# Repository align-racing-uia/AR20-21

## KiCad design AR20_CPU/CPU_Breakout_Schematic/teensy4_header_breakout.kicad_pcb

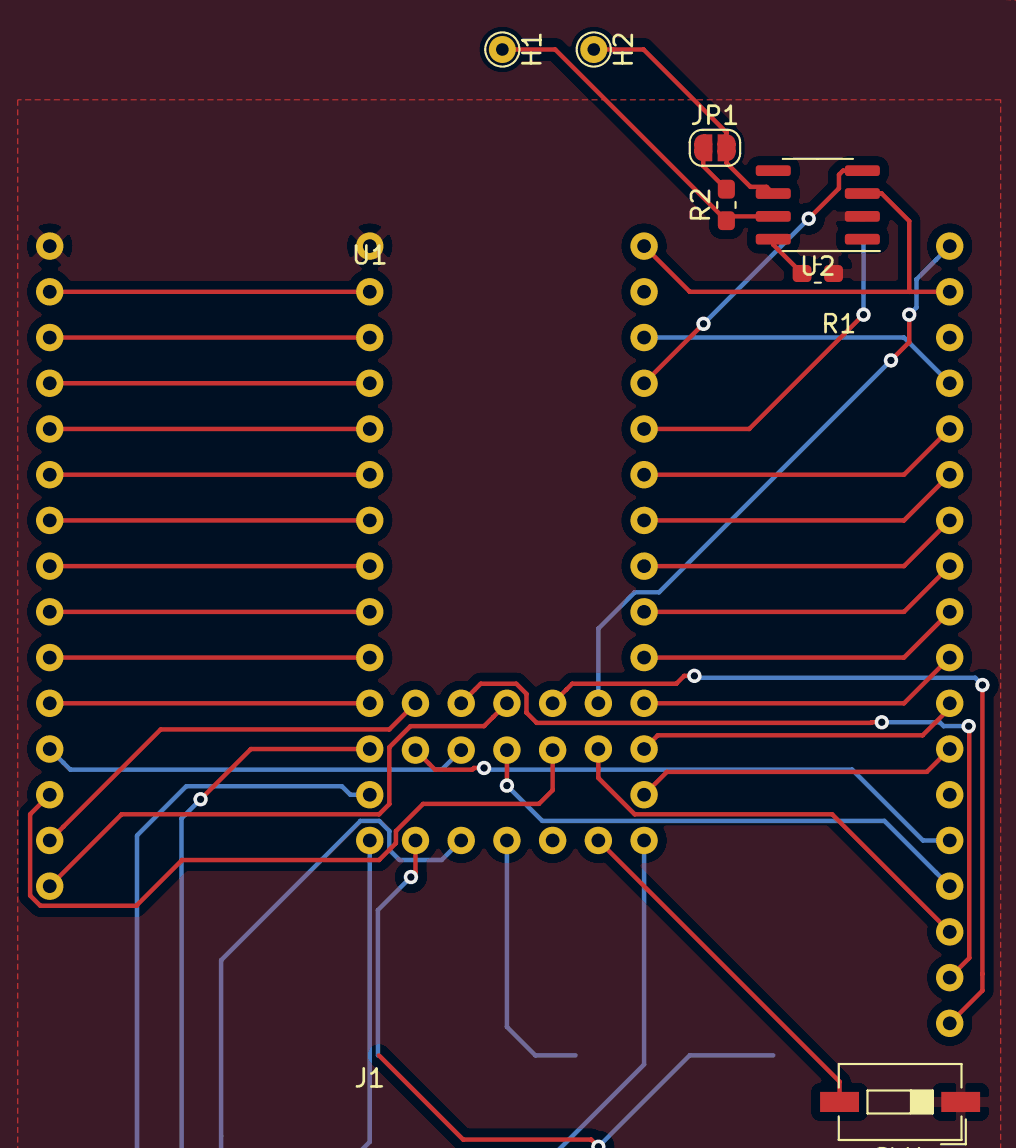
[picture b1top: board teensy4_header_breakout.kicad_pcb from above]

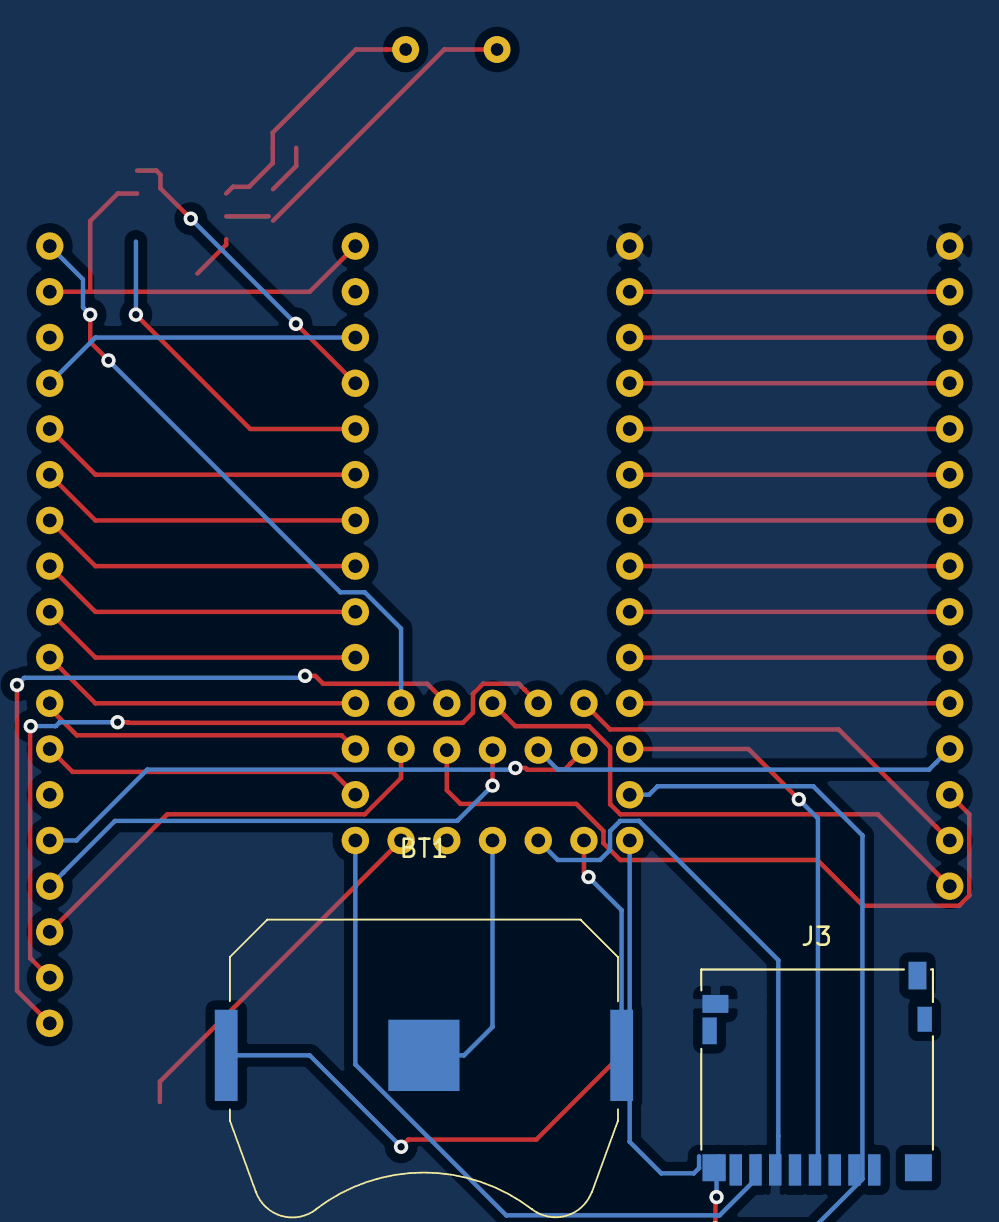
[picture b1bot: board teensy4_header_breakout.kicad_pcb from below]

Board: 4 copper layers, 11 parts (2 on the bottom side), 47 nets.

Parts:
BT1: 2.7V; BatteryHolder_Keystone_3034_1x20mm
H1: CANH_out; TestPoint_THTPad_D1.5mm_Drill0.7mm
H2: CANL_out; TestPoint_THTPad_D1.5mm_Drill0.7mm
J1: Conn_2Rows-34Pins; PINS_IO_TEENSY
J3: Micro_SD_Card; microSD_HC_Hirose_DM3D-SF
JP1: SolderJumper_2_Open; SolderJumper-2_P1.3mm_Open_RoundedPad1.0x1.5mm
R1: 60; R_0603_1608Metric_Pad1.05x0.95mm_HandSolder
R2: 120; R_0603_1608Metric_Pad1.05x0.95mm_HandSolder
SW1: SW_SPST; SW_DIP_SPSTx01_Slide_6.7x4.1mm_W6.73mm_P2.54mm_LowProfile_J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
U1: Teensy_pins; Teensy_40_footprint
U2: MCP2551-I-SN; SOIC-8_3.9x4.9mm_P1.27mm

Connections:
0_RX1: J1.3, U1.3
1_TX1: J1.5, U1.5
2_OUT2: J1.7, U1.7
3.3V: J1.12, U1.6
3V3: J3.4, U1.30
3_LRCLK2: J1.9, U1.9
4_BCLK2: J1.11, U1.11
5_IN2: J1.13, U1.13
6_OUT1D: J1.15, U1.15
7_RX2_OUT1A: J1.17, U1.17
8_IN1: J1.19, U1.19
9_OUT1C: J1.21, U1.21
10_CS: J3.2, U1.23
11_MOSI: J3.7, U1.25
12_MISO: J3.8, U1.27
13(LED): J3.5, U1.28
14_A0: J1.28, U1.26
15_A1: J1.26, U1.24
16_A2: J1.24, U1.22
17_A3: J1.22, U1.20
18_A4: J1.20, U1.18
19_A5: J1.18, U1.16
20_A6: J1.16, U1.14
21_A7: J1.14, U1.12
22_CTX1: U1.10, U2.1
23_CRX1: U1.8, U2.4
24_A10: J1.34, U1.34
25_A11: J1.35, U1.35
26_A12: J1.36, U1.36
27_A13: J1.37, U1.37
28_RX7: J1.38, U1.38
29_TX7: J1.39, U1.39
30_CRX3: J1.40, U1.40
31_CTX3: J1.41, U1.41
32_OUT1B: J1.42, U1.42
33_MCLK2: J1.2, U1.43
GND_1: J1.6, U1.4
GND_BATT: BT1.2, U1.31
Ground: J1.1, J3.6, J3.9, R1.1, SW1.1, U1.1, U2.2
unnamed: H1.1, R2.1, U2.7
unnamed: H2.1, JP1.2, U2.6
unnamed: JP1.1, R2.2
unnamed: R1.2, U2.8
ON_OFF: SW1.2, U1.33
PROGRAMM: J1.32, U1.32
VBAT: BT1.1, U1.29
Vinn_5V: J1.4, U1.2, U2.3

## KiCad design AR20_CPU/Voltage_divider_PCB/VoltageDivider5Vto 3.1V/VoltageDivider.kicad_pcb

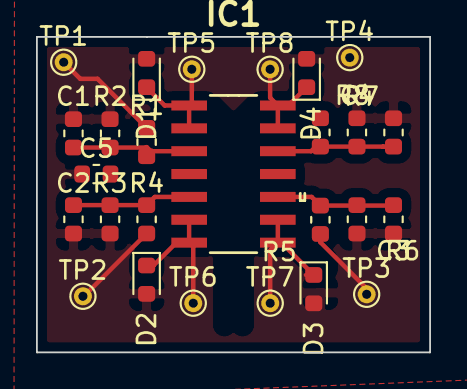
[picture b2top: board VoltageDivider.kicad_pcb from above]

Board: 2 copper layers, 21.8 x 17.5 mm, 26 parts (0 on the bottom side), 13 nets.

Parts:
C1, C2, C3, C4: 1.5n; C_0603_1608Metric
C5: C; C_0603_1608Metric
D1, D2, D3, D4: 3V; D_0603_1608Metric
IC1: LM324DRG3; SOIC127P600X175-14N
R1, R3, R5, R7: 10k; R_0603_1608Metric
R2, R4, R6, R8: 20k; R_0603_1608Metric
TP1, TP2, TP3, TP4, TP5, TP6, TP7, TP8: TestPoint; TestPoint_THTPad_D1.0mm_Drill0.5mm

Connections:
GND: C1.2, C2.2, C3.2, C4.2, C5.1, D1.2, D2.2, D3.2, D4.2, R2.2, R4.2, R6.2, R8.2
IN1+: C1.1, IC1.3, R1.2, R2.1
IN2+: C2.1, IC1.5, R3.2, R4.1
IN3+: C3.1, IC1.10, R5.2, R6.1
IN4+: C4.1, IC1.12, R7.2, R8.1
Out1: D1.1, IC1.1, IC1.2, TP5.1
Out2: D2.1, IC1.6, IC1.7, TP6.1
Out3: D3.1, IC1.8, IC1.9, TP7.1
Out4: D4.1, IC1.13, IC1.14, TP8.1
Sensor_Input_1: R1.1, TP1.1
Sensor_Input_2: R3.1, TP2.1
Sensor_Input_3: R5.1, TP3.1
Sensor_Input_4: R7.1, TP4.1

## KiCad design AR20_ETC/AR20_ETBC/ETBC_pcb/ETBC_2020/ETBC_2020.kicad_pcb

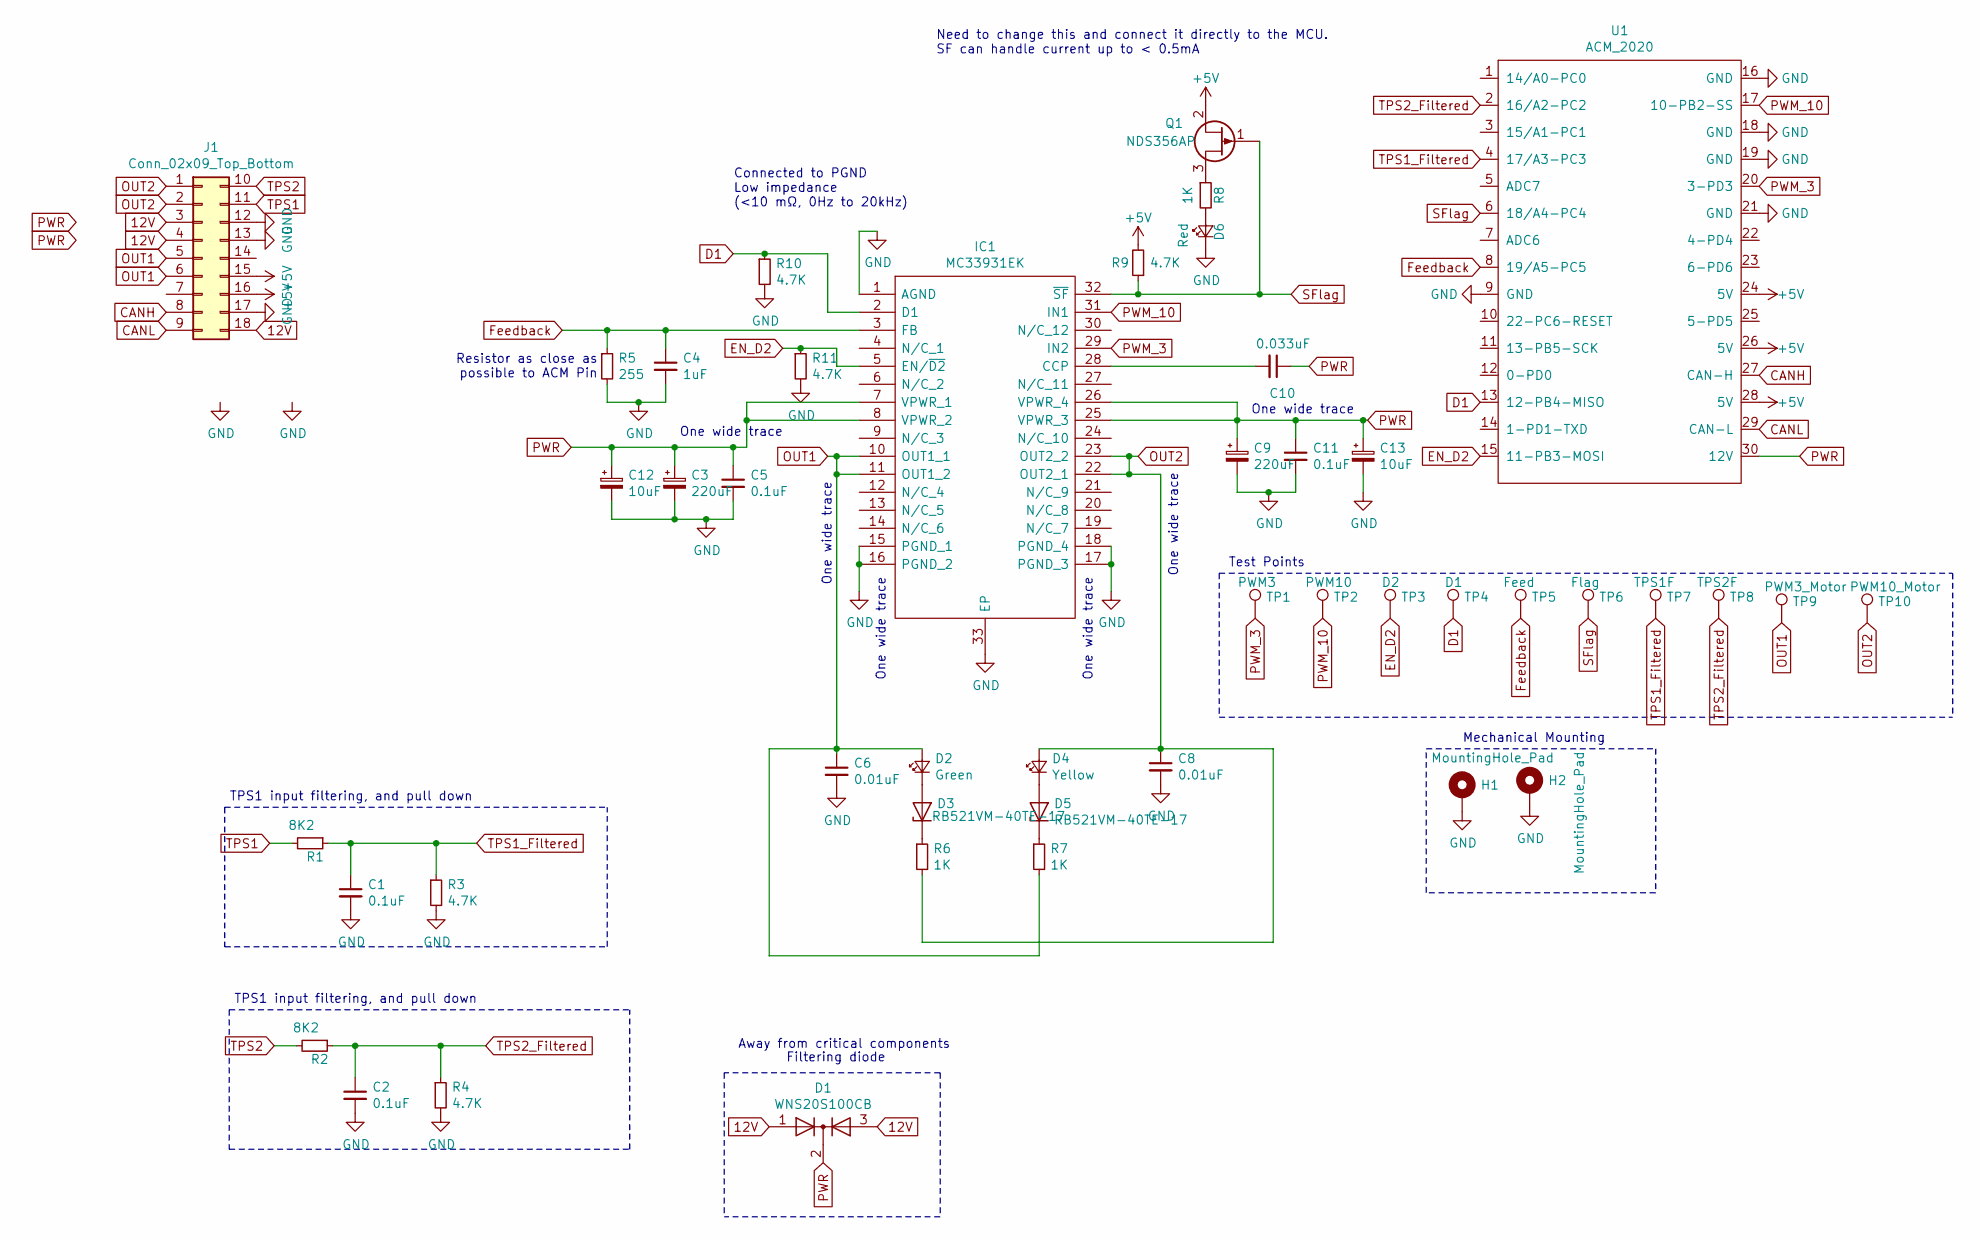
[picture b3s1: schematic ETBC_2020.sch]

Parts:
C1, C2, C5, C11: 0.1uF; C_0603_1608Metric_Pad1.05x0.95mm_HandSolder
C3, C9: 220uF; CP_Elec_6.3x7.7
C4: 1uF; C_0603_1608Metric_Pad1.05x0.95mm_HandSolder
C6, C8: 0.01uF; C_0603_1608Metric_Pad1.05x0.95mm_HandSolder
C10: 0.033uF; C_0603_1608Metric_Pad1.05x0.95mm_HandSolder
C12, C13: 10uF; CP_EIA-3216-10_Kemet-I_Pad1.58x1.35mm_HandSolder
D1: WNS20S100CB; TO-263-3_TabPin2
D2: Green; D_1206_3216Metric_Pad1.42x1.75mm_HandSolder
D3, D5: RB521VM-40TE-17; D_SOD-323F
D4: Yellow; D_1206_3216Metric_Pad1.42x1.75mm_HandSolder
D6: Red; D_1206_3216Metric_Pad1.42x1.75mm_HandSolder
H1, H2: MountingHole_Pad; MountingHole_3.2mm_M3_Pad_Via
IC1: MC33931EK; SOP65P1030X245-33N; Manufacturer_Part_Number MC33931EK; Mouser Part Number 841-MC33931EK
J1: Conn_02x09_Top_Bottom; JAE_MX23A18NF1
Q1: NDS356AP; SOT-23
R1, R2: 8K2; R_0603_1608Metric_Pad1.05x0.95mm_HandSolder
R3, R4, R9, R10, R11: 4.7K; R_0603_1608Metric_Pad1.05x0.95mm_HandSolder
R5: 255; R_0603_1608Metric_Pad1.05x0.95mm_HandSolder
R6, R7, R8: 1K; R_0603_1608Metric_Pad1.05x0.95mm_HandSolder
TP1: PWM3; TestPoint_Keystone_5000-5004_Miniature
TP2: PWM10; TestPoint_Keystone_5000-5004_Miniature
TP3: D2; TestPoint_Keystone_5000-5004_Miniature
TP4: D1; TestPoint_Keystone_5000-5004_Miniature
TP5: Feed; TestPoint_Keystone_5000-5004_Miniature
TP6: Flag; TestPoint_Keystone_5000-5004_Miniature
TP7: TPS1F; TestPoint_Keystone_5000-5004_Miniature
TP8: TPS2F; TestPoint_Keystone_5000-5004_Miniature
TP9: PWM3_Motor; TestPoint_Keystone_5000-5004_Miniature
TP10: PWM10_Motor; TestPoint_Keystone_5000-5004_Miniature
U1: ACM_2020; ACM_2020_Footprint_wo_silk

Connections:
12V: D1.1 (A), D1.3 (A), J1.3, J1.4, J1.18
+5V: J1.15, J1.16, Q1.2 (S), R9.2, U1.24 (5V), U1.26 (5V), U1.28 (5V)
CANH: J1.8, U1.27 (CAN-H)
CANL: J1.9, U1.29 (CAN-L)
D1: IC1.2 (D1), R10.1, TP4.1, U1.13 (12-PB4-MISO)
EN_D2: IC1.5 (EN/~D2), R11.1, TP3.1, U1.15 (11-PB3-MOSI)
Feedback: C4.1, IC1.3 (FB), R5.1, TP5.1, U1.8 (19/A5-PC5)
GND: C1.2, C2.2, C3.2, C4.2, C5.2, C6.2, C8.2, C9.2, C11.2, C12.2, C13.2, D6.1 (K), H1.1, H2.1, IC1.1 (AGND), IC1.15 (PGND_1), IC1.16 (PGND_2), IC1.17 (PGND_3), IC1.18 (PGND_4), IC1.33 (EP), J1.12, J1.13, J1.17, R3.2, R4.2, R5.2, R10.2, R11.2, U1.9 (GND), U1.16 (GND), U1.18 (GND), U1.19 (GND), U1.21 (GND)
unnamed: C10.2, IC1.28 (CCP)
unnamed: D2.1 (K), D3.2 (A)
unnamed: D3.1 (K), R6.1
unnamed: D4.1 (K), D5.2 (A)
unnamed: D5.1 (K), R7.1
unnamed: D6.2 (A), R8.2
unnamed: Q1.3 (D), R8.1
OUT1: C6.1, D2.2 (A), IC1.10 (OUT1_1), IC1.11 (OUT1_2), J1.5, J1.6, R7.2, TP9.1
OUT2: C8.1, D4.2 (A), IC1.22 (OUT2_1), IC1.23 (OUT2_2), J1.1, J1.2, R6.2, TP10.1
PWM_3: IC1.29 (IN2), TP1.1, U1.20 (3-PD3)
PWM_10: IC1.31 (IN1), TP2.1, U1.17 (10-PB2-SS)
PWR: C3.1, C5.1, C9.1, C10.1, C11.1, C12.1, C13.1, D1.2 (K), IC1.7 (VPWR_1), IC1.8 (VPWR_2), IC1.25 (VPWR_3), IC1.26 (VPWR_4), U1.30 (12V)
SFlag: IC1.32 (~SF), Q1.1 (G), R9.1, TP6.1, U1.6 (18/A4-PC4)
TPS1: J1.11, R1.2
TPS1_Filtered: C1.1, R1.1, R3.1, TP7.1, U1.4 (17/A3-PC3)
TPS2: J1.10, R2.2
TPS2_Filtered: C2.1, R2.1, R4.1, TP8.1, U1.2 (16/A2-PC2)

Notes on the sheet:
TPS1 input filtering, and pull down
Resistor as close as possible to ACM Pin
Filtering diode
Connected to PGND Low impedance (<10 mΩ, 0Hz to 20kHz)
One wide trace
Need to change this and connect it directly to the MCU. SF can handle current up to < 0.5mA
Away from critical components
Mechanical Mounting
Test Points

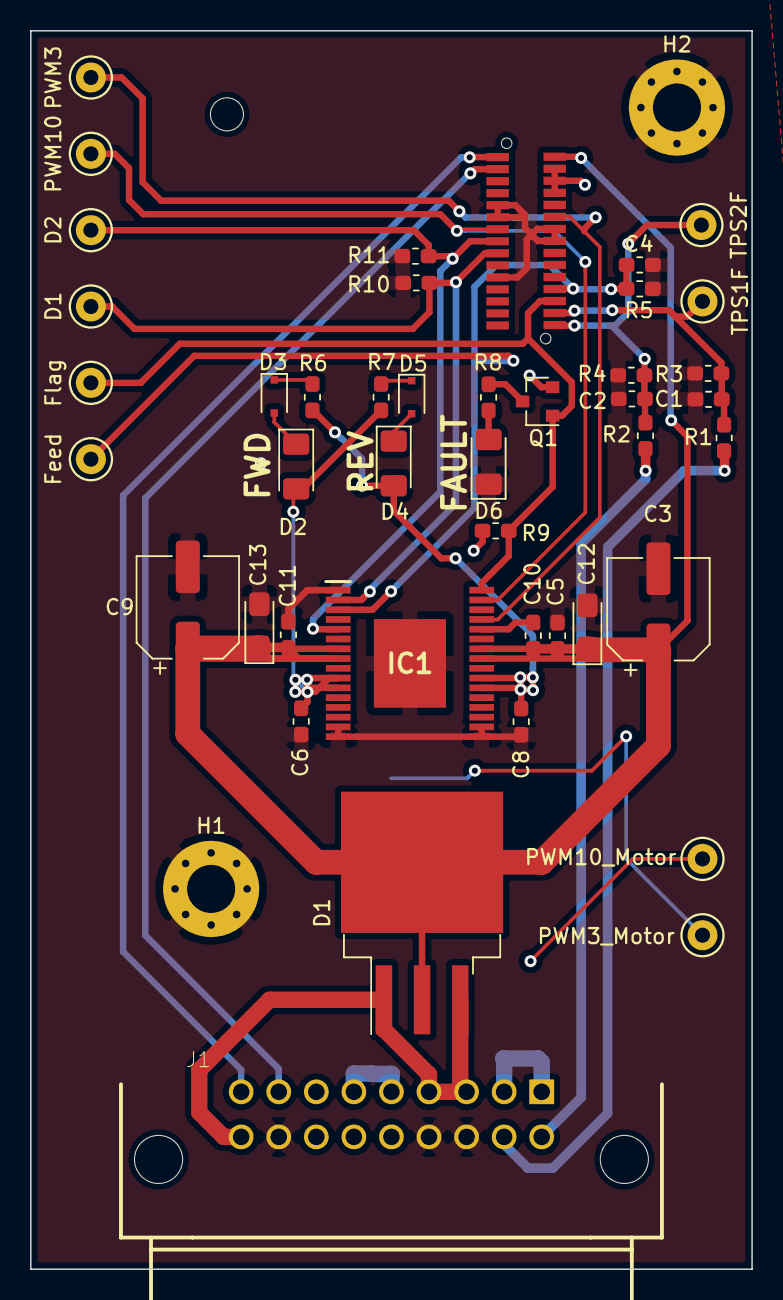
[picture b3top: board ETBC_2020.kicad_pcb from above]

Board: 2 copper layers, 48.0 x 82.4 mm, 45 parts (0 on the bottom side), 25 nets.

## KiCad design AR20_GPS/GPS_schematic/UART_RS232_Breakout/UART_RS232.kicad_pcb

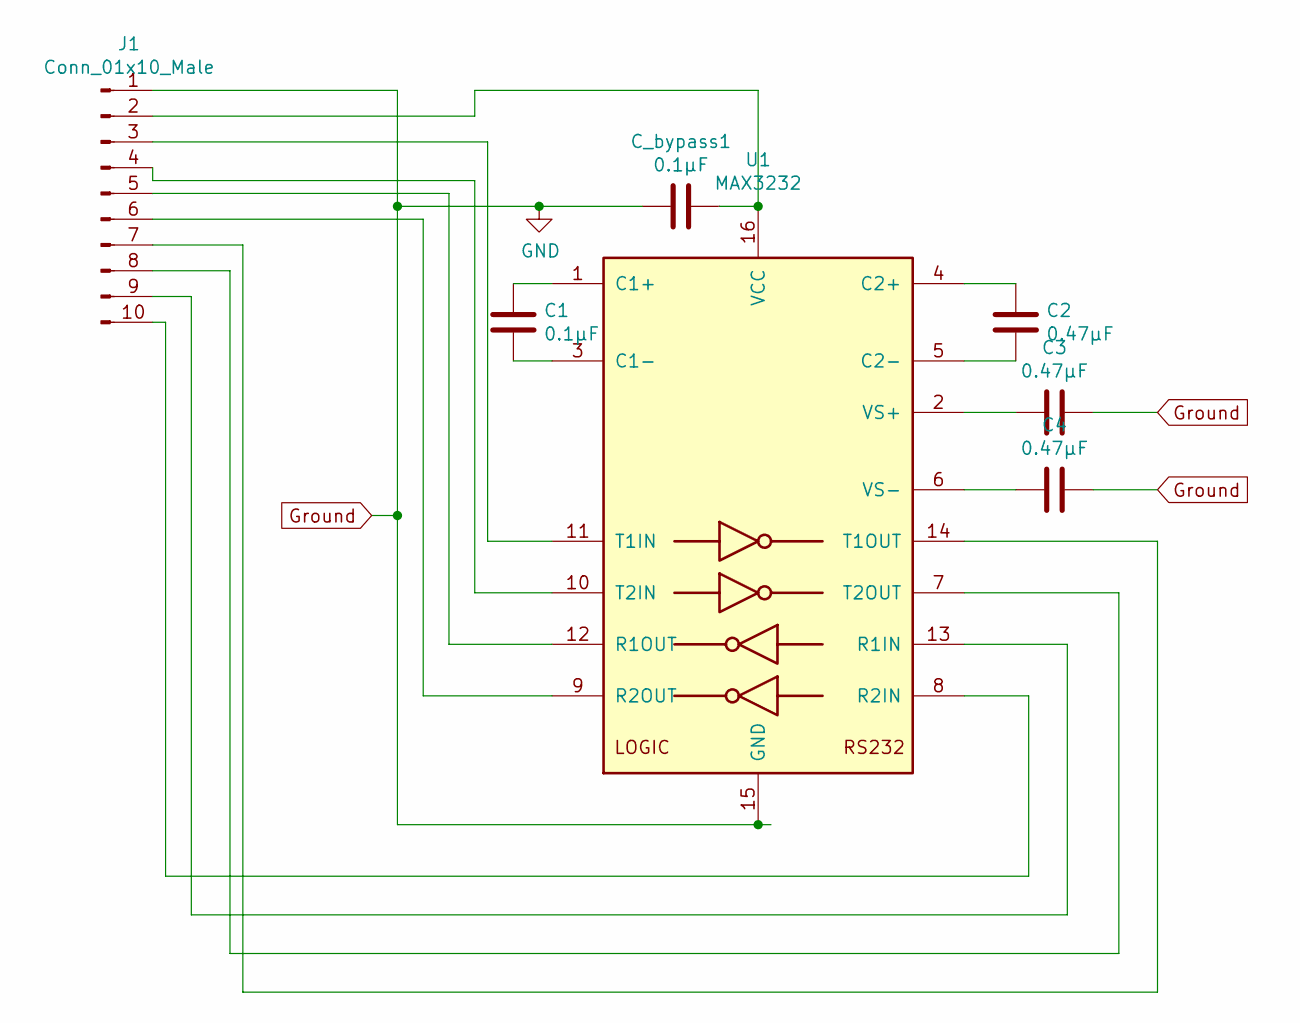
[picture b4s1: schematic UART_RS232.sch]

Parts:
C1: 0.1µF; C_Disc_D8.0mm_W5.0mm_P5.00mm
C2, C3, C4: 0.47µF; C_Disc_D8.0mm_W5.0mm_P5.00mm
C_bypass1: 0.1µF; C_Disc_D8.0mm_W5.0mm_P5.00mm
J1: Conn_01x10_Male; PinHeader_1x10_P2.54mm_Horizontal
U1: MAX3232; DIP-16_W7.62mm

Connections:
Ground: C3.2, C4.2, C_bypass1.1, J1.1, U1.15 (GND)
unnamed: C1.1, U1.1 (C1+)
unnamed: C1.2, U1.3 (C1-)
unnamed: C2.1, U1.4 (C2+)
unnamed: C2.2, U1.5 (C2-)
unnamed: C3.1, U1.2 (VS+)
unnamed: C4.1, U1.6 (VS-)
unnamed: C_bypass1.2, J1.2, U1.16 (VCC)
unnamed: J1.3, U1.11 (T1IN)
unnamed: J1.4, U1.10 (T2IN)
unnamed: J1.5, U1.12 (R1OUT)
unnamed: J1.6, U1.9 (R2OUT)
unnamed: J1.7, U1.14 (T1OUT)
unnamed: J1.8, U1.7 (T2OUT)
unnamed: J1.9, U1.13 (R1IN)
unnamed: J1.10, U1.8 (R2IN)

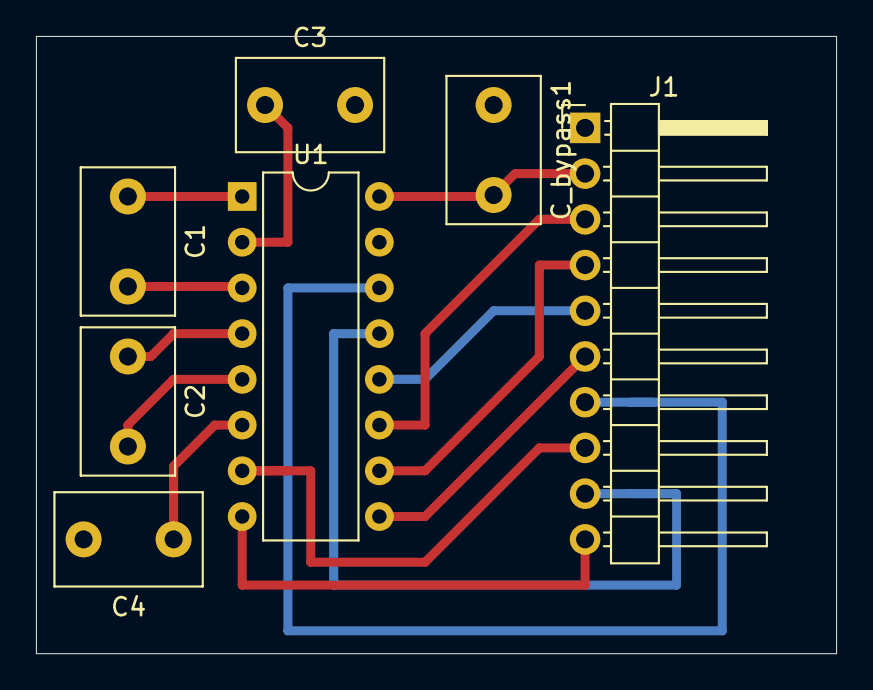
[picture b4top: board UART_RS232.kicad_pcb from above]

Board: 2 copper layers, 44.5 x 34.3 mm, 7 parts (0 on the bottom side), 16 nets.

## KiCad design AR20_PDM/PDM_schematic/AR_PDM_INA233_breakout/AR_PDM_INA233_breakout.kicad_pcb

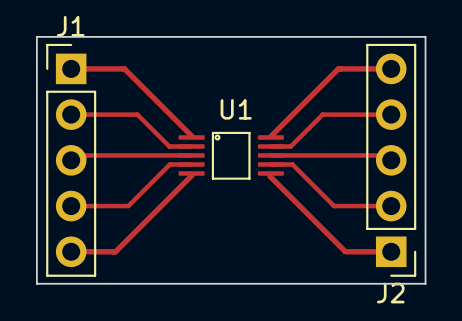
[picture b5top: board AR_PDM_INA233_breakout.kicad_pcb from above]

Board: 2 copper layers, 21.6 x 13.7 mm, 3 parts (0 on the bottom side), 10 nets.

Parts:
J1, J2: Conn_01x05_Male; PinHeader_1x05_P2.54mm_Vertical
U1: INA233

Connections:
GND: J2.2, U1.7
IN+: J2.5, U1.10
IN-: J2.4, U1.9
unnamed: J1.1, U1.1
unnamed: J1.2, U1.2
unnamed: J1.3, U1.3
unnamed: J1.4, U1.4
unnamed: J1.5, U1.5
VBUS: J2.3, U1.8
VS: J2.1, U1.6

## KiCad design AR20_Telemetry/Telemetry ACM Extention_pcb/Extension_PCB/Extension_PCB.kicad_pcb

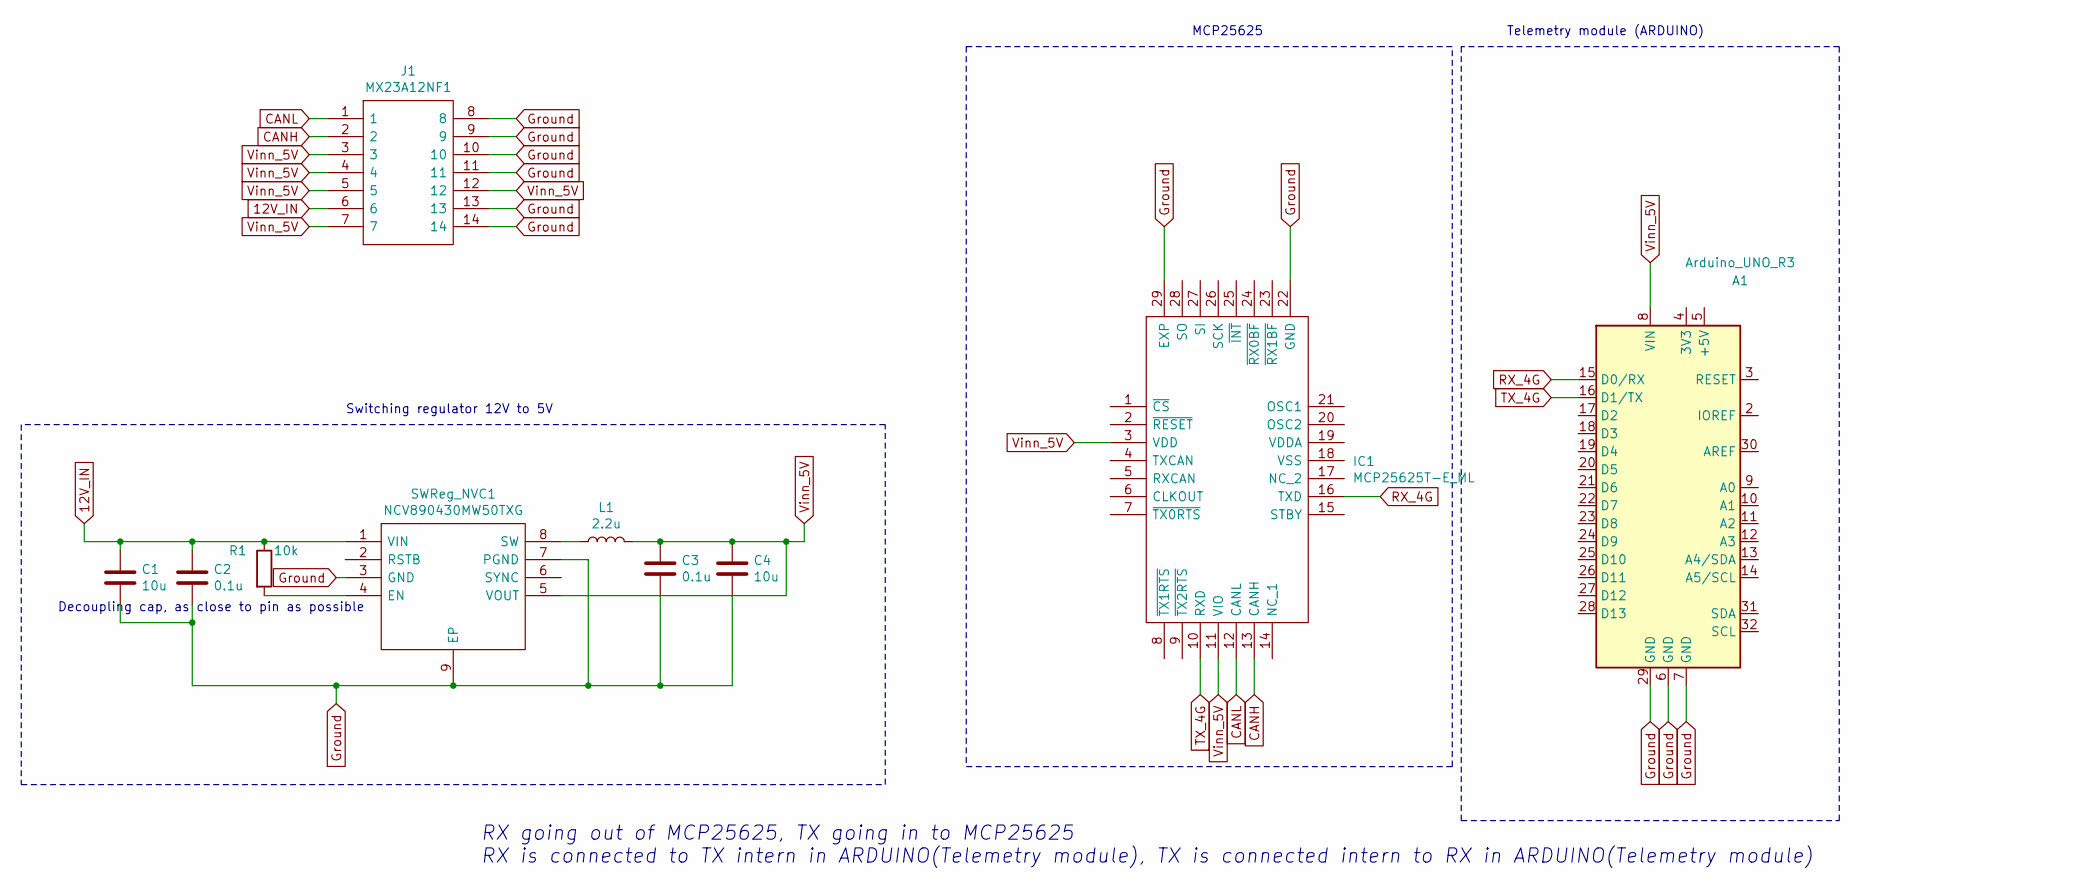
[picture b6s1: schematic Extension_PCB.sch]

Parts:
A1: Arduino_UNO_R3; Arduino_UNO_R3_WithMountingHoles_telemetry
C1, C4: 10u; C_0603_1608Metric
C2, C3: 0.1u; C_0603_1608Metric
IC1: MCP25625T-E_ML; QFN65P600X600X100-29N-D; Manufacturer_Part_Number MCP25625T-E/ML; Mouser Part Number 579-MCP25625T-E/ML
J1: MX23A12NF1; Manufacturer_Part_Number MX23A12NF1; Mouser Part Number 656-MX23A12NF1
L1: 2.2u; L_0603_1608Metric
R1: 10k; R_0603_1608Metric
SWReg_NVC1: NCV890430MW50TXG; DFN-8-1EP_3x3mm_P0.65mm_EP1.7x2.05mm; Manufacturer_Part_Number NCV890430MW50TXG; Mouser Part Number 863-NCV890430MW50TXG

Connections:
12V_IN: C1.1, C2.1, J1.6, R1.1, SWReg_NVC1.1 (VIN)
CANH: IC1.13 (CANH), J1.2
CANL: IC1.12 (CANL), J1.1
Ground: A1.6 (GND), A1.7 (GND), A1.29 (GND), C1.2, C2.2, C3.2, C4.2, IC1.22 (GND), IC1.29 (EXP), J1.8, J1.9, J1.10, J1.11, J1.13, J1.14, SWReg_NVC1.3 (GND), SWReg_NVC1.7 (PGND), SWReg_NVC1.9 (EP)
unnamed: L1.1, SWReg_NVC1.8 (SW)
unnamed: R1.2, SWReg_NVC1.4 (EN)
RX_4G: A1.15 (D0/RX), IC1.16 (TXD)
TX_4G: A1.16 (D1/TX), IC1.10 (RXD)
Vinn_5V: A1.8 (VIN), C3.1, C4.1, IC1.3 (VDD), IC1.11 (VIO), J1.3, J1.4, J1.5, J1.7, J1.12, L1.2, SWReg_NVC1.5 (VOUT)

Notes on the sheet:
Decoupling cap, as close to pin as possible
RX going out of MCP25625, TX going in to MCP25625 RX is connected to TX intern in ARDUINO(Telemetry module), TX is connected intern to RX in ARDUINO(Telemetry module)
MCP25625
Telemetry module (ARDUINO)
Switching regulator 12V to 5V

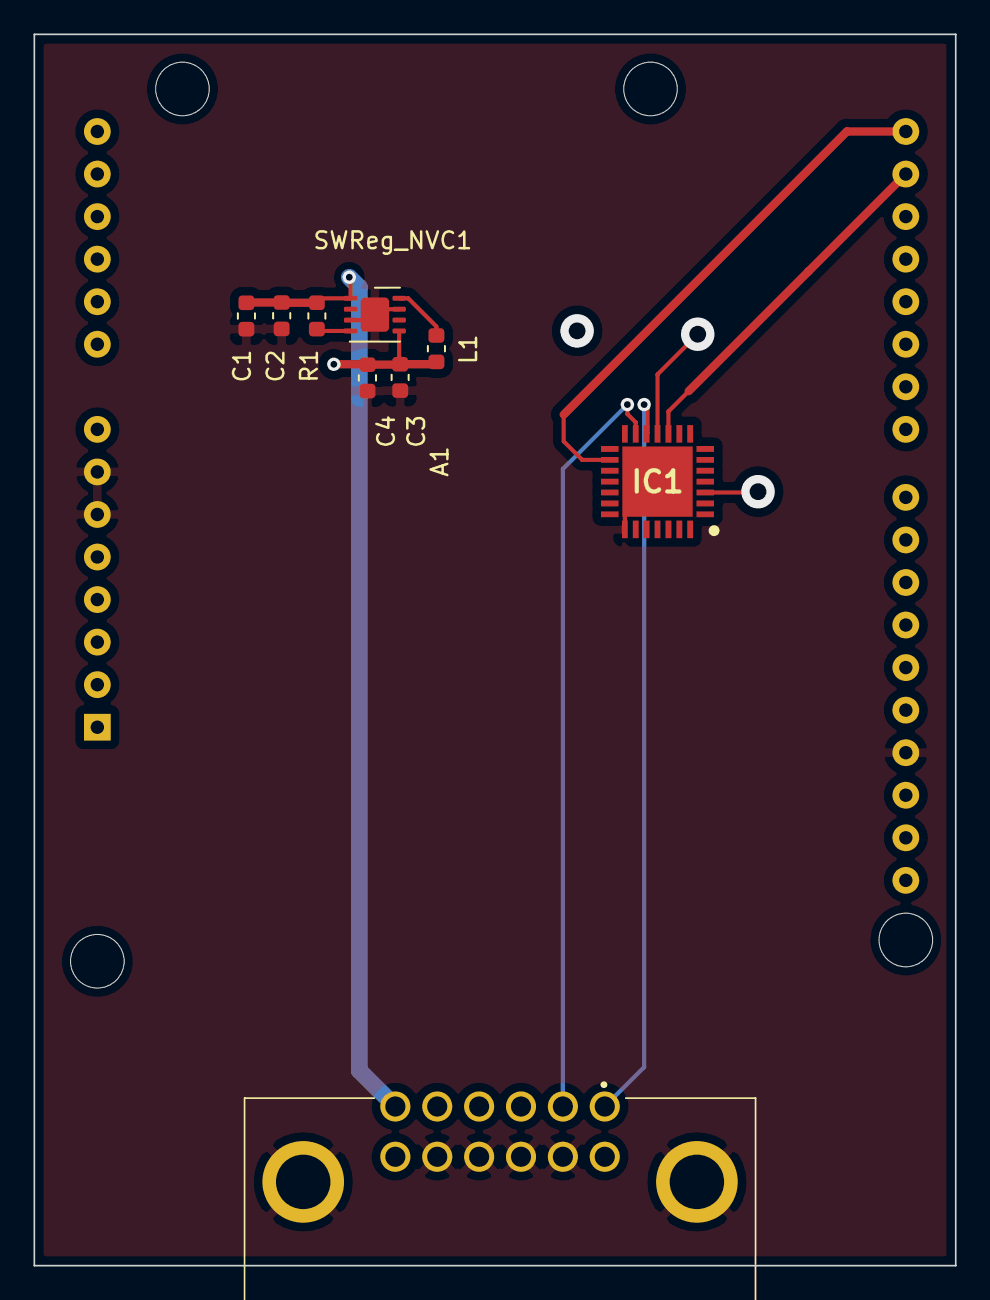
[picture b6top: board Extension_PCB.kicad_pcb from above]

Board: 2 copper layers, 55.0 x 73.5 mm, 10 parts (0 on the bottom side), 9 nets.

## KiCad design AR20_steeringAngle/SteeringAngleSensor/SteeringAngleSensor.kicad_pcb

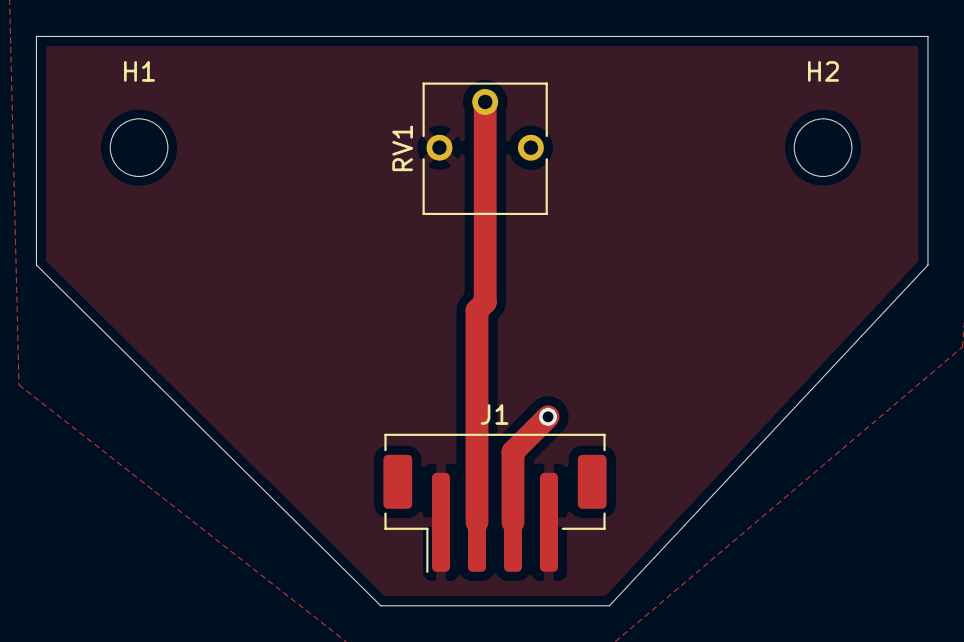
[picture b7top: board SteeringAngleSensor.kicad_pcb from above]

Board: 2 copper layers, 49.5 x 31.6 mm, 4 parts (0 on the bottom side), 3 nets.

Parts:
H1, H2: MountingHole; MountingHole_3.2mm_M3
J1: Conn_01x04_Male; JST_PH_B4B-PH-SM4-TB_1x04-1MP_P2.00mm_Vertical
RV1: R_POT; Potentiometer_Vishay_T73YP_Vertical

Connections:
/5V: J1.3, RV1.1
/GND: J1.1, J1.4, RV1.3
/Out: J1.2, RV1.2
